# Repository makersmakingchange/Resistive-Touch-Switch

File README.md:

# Resistive Touch Switch

The Resistive Touch Switch is an open-source assistive switch that is activated through skin contact. The switch requires minimal force to activate.

## More info at

- [Makers Making Change Project Page](https://www.makersmakingchange.com/project/resistive-touch-switch/)

<!-- ABOUT MMC START -->
## About Makers Making Change

Makers Making Change is a program of [Neil Squire](https://www.neilsquire.ca/), a Canadian non-profit that uses technology, knowledge, and passion to empower people with disabilities.

Makers Making Change leverages the capacity of community based Makers, Disability Professionals and Volunteers to develop and deliver affordable Open Source Assistive Technologies.

 - Website: [www.MakersMakingChange.com](https://www.makersmakingchange.com/)
 - GitHub: [makersmakingchange](https://github.com/makersmakingchange)
 - Bluesky: [@makersmakingchange.bsky.social](https://bsky.app/profile/makersmakingchange.bsky.social)
 - Instagram: [@makersmakingchange](https://www.instagram.com/makersmakingchange)
 - Facebook: [makersmakechange](https://www.facebook.com/makersmakechange)
 - LinkedIn: [Neil Squire Society](https://www.linkedin.com/company/neil-squire-society/)
 - Thingiverse: [makersmakingchange](https://www.thingiverse.com/makersmakingchange/about)
 - Printables: [MakersMakingChange](https://www.printables.com/@MakersMakingChange)

### Contact Us
For technical questions, to get involved, or to share your experience we encourage you to [visit our website](https://www.makersmakingchange.com/) or [contact us](https://www.makersmakingchange.com/s/contact).
<!-- ABOUT MMC END -->

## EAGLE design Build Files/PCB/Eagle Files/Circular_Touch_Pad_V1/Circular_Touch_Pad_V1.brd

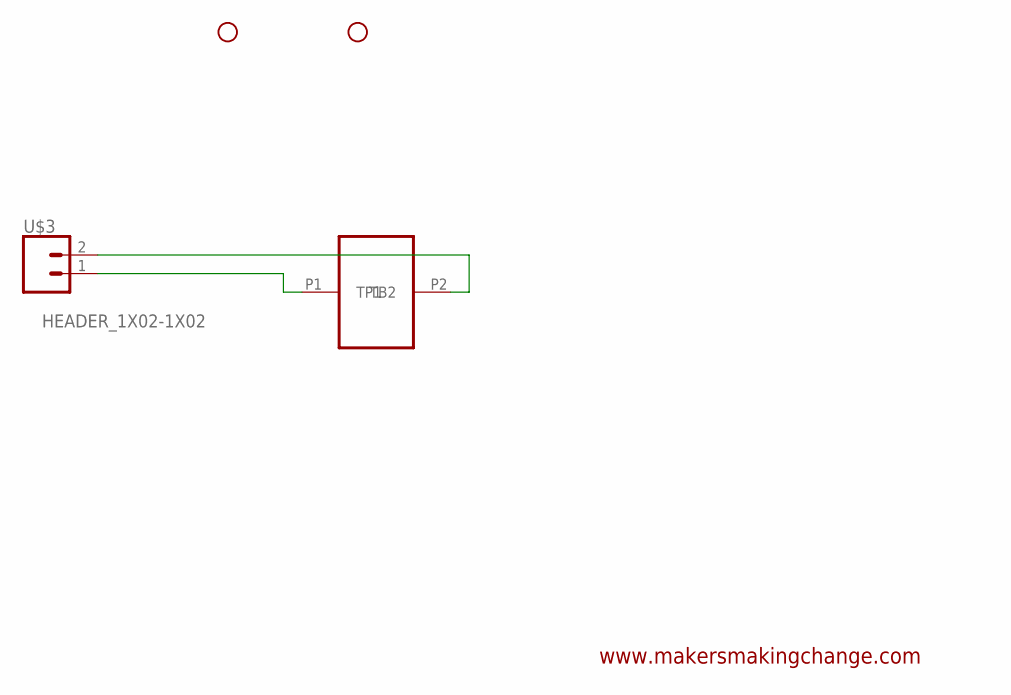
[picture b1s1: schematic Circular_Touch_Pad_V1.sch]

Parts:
H1, H2: STAND-OFF-; STAND-OFF
U$1: TOUCHPAD-CIRCLE; TOUCHPAD-CIRCLE-VER1
U$3: HEADER_1X02-1X02; 1X02

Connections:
unnamed: U$1.P1 (TP1), U$3.1
unnamed: U$1.P2 (TB2), U$3.2

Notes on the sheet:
www.makersmakingchange.com

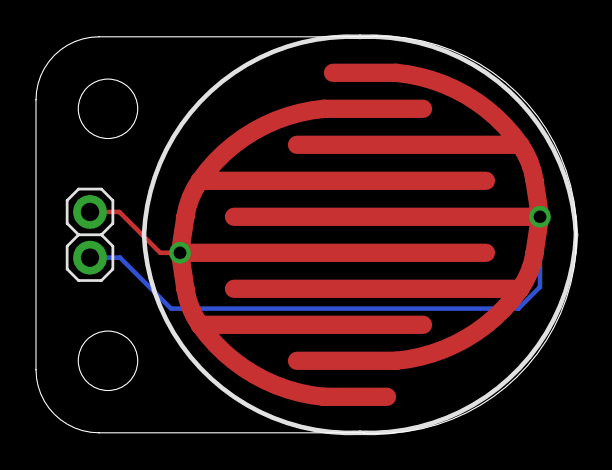
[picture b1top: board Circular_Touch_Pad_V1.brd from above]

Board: 2 copper layers, 30.0 x 22.1 mm, 4 parts (0 on the bottom side), 2 nets.

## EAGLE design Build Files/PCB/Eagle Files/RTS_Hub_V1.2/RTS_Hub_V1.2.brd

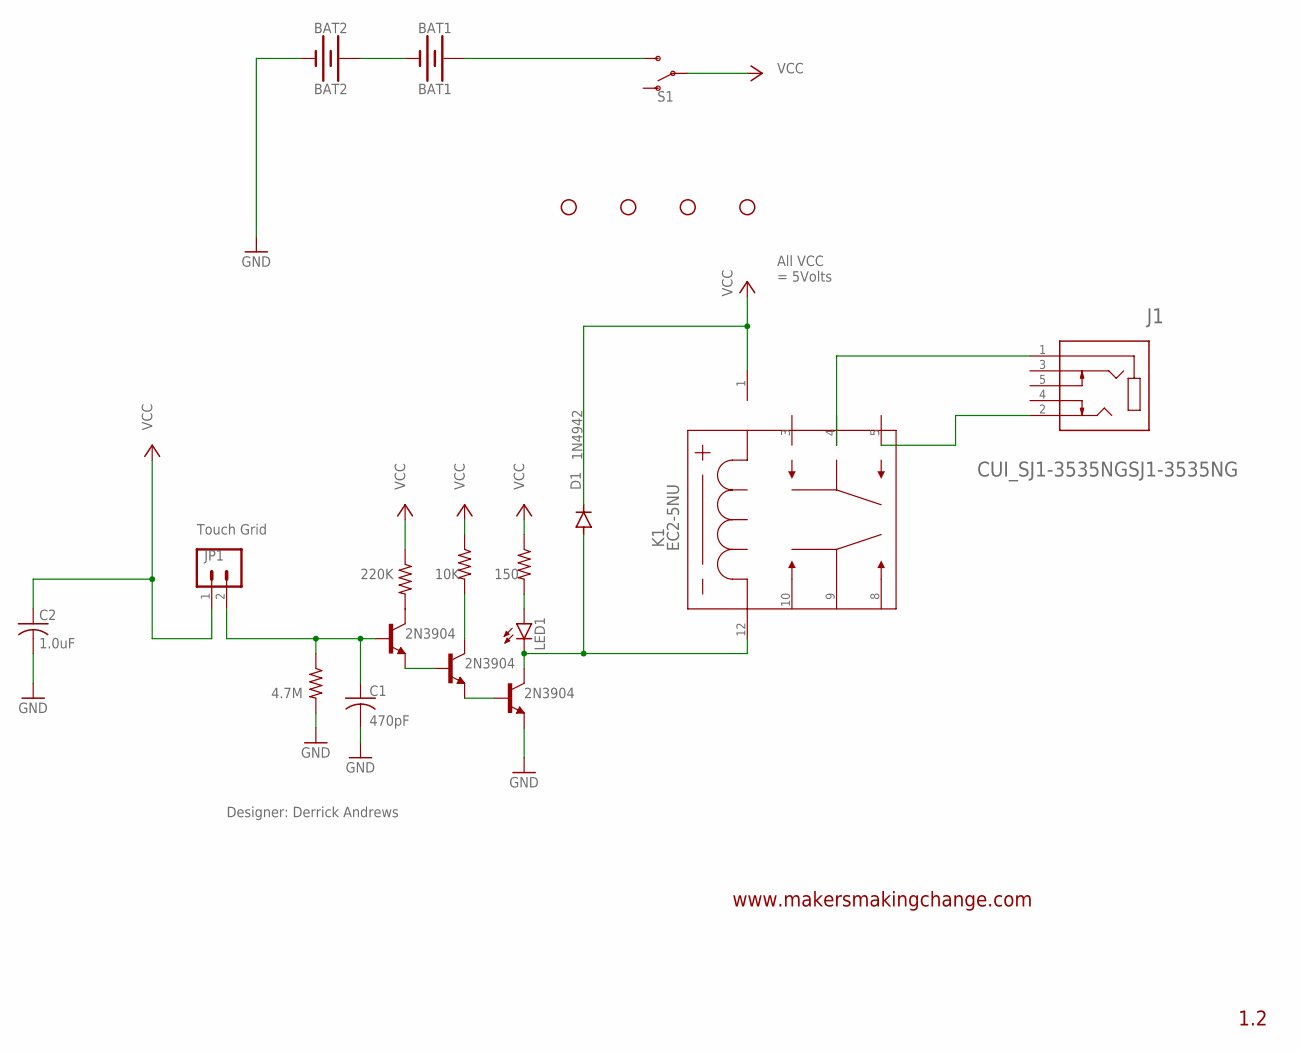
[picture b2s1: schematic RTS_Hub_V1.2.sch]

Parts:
BAT1: BAT1; BATTCOM_20MM_PTH
BAT2: BAT2; BATTCOM_20MM_PTH
C1: 470pF; C025-030X050
C2: 1.0uF; C050-030X075
D1: 1N4942; DO41-10
H1, H2, H3, H4: STAND-OFF-; STAND-OFF
J1: CUI_SJ1-3535NGSJ1-3535NG; CUI_SJ1-3535NG
JP1: HEADER_1X02-1X02; 1X02
K1: EC2-5NU; EC2NU
LED1: LED5MM; LED_5MM
R1: 10K; RESISTOR_0207/7
R2: 4.7M; RESISTOR_0207/7
R3: 220K; RESISTOR_0207/7
R4: 150; RESISTOR_0207/7
S1: SWITCH-SPDT-PTH_11.6X4.0MM; SWITCH_SPDT_PTH_11.6X4.0MM
T1, T2, T3: 2N3904; TO92-CBE

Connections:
GND: BAT2.-, C1.2, C2.2, R2.2, T1.E
unnamed: T2.B, T3.E
unnamed: T1.B, T2.E
unnamed: D1.A, K1.12 (8), LED1.K (C), T1.C
unnamed: R1.2, T2.C
unnamed: R3.2, T3.C
unnamed: LED1.A, R4.2
unnamed: C1.1, JP1.2, R2.1, T3.B
unnamed: BAT1.+, S1.3 (S)
unnamed: J1.1, K1.4 (3)
unnamed: J1.2, K1.5 (4)
unnamed: BAT1.-, BAT2.+
VCC: C2.1, D1.C, JP1.1, K1.1, R1.1, R3.1, R4.1, S1.2

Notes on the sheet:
150
220K
10K
Touch Grid
4.7M
All VCC = 5Volts
Designer: Derrick Andrews
www.makersmakingchange.com
1.2

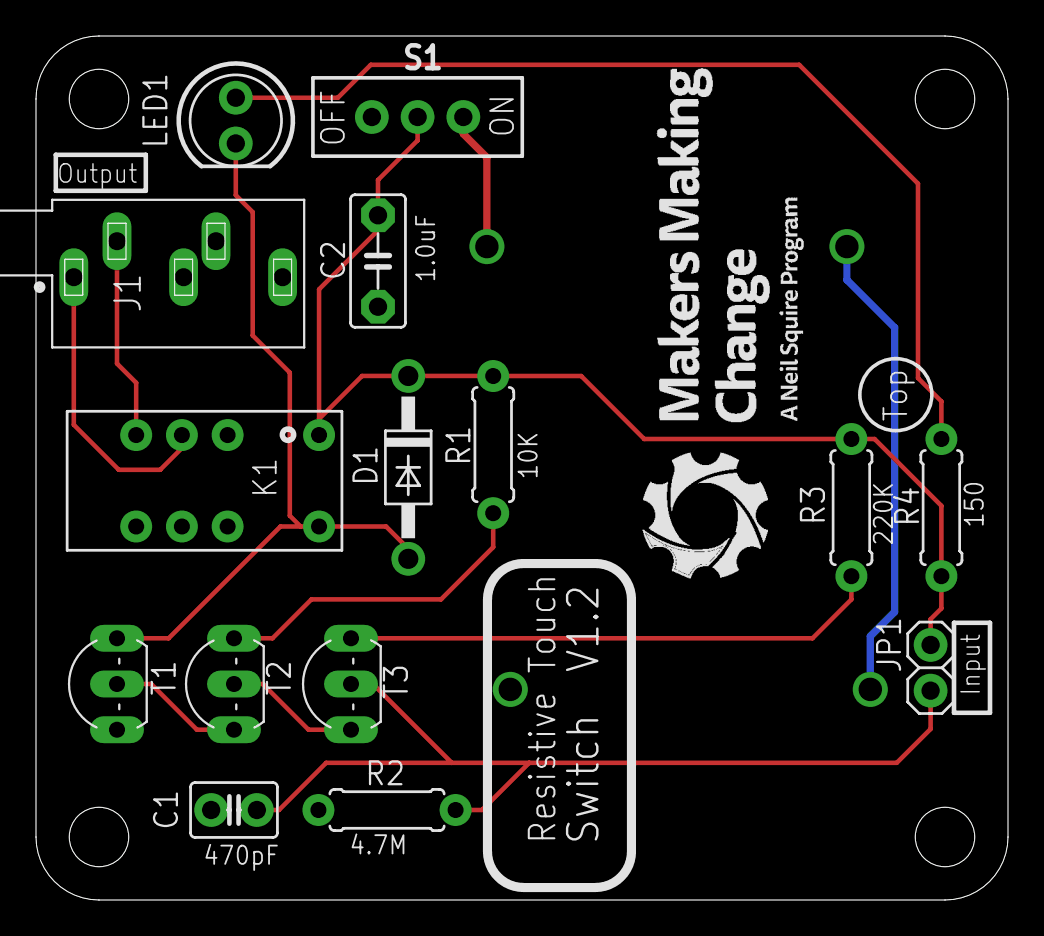
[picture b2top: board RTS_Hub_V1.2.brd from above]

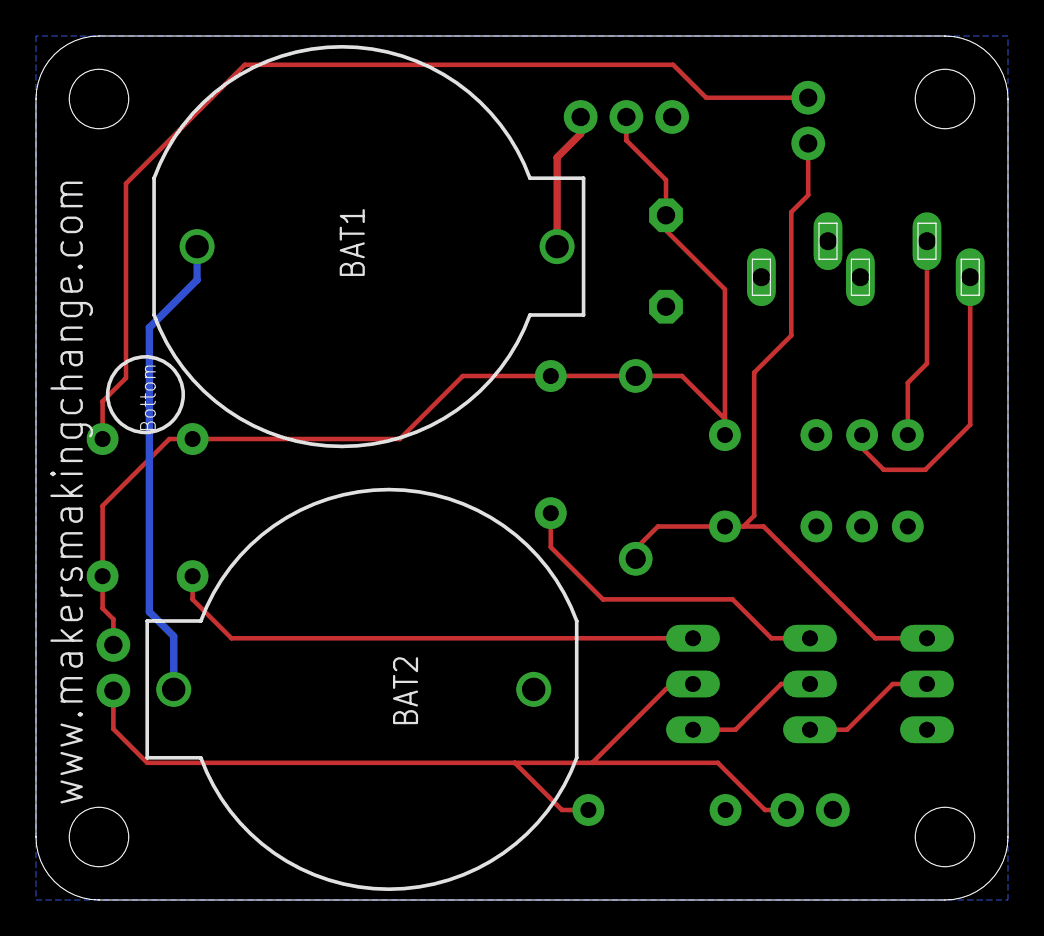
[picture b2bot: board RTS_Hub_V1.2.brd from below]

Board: 2 copper layers, 54.0 x 48.0 mm, 21 parts (2 on the bottom side), 13 nets.

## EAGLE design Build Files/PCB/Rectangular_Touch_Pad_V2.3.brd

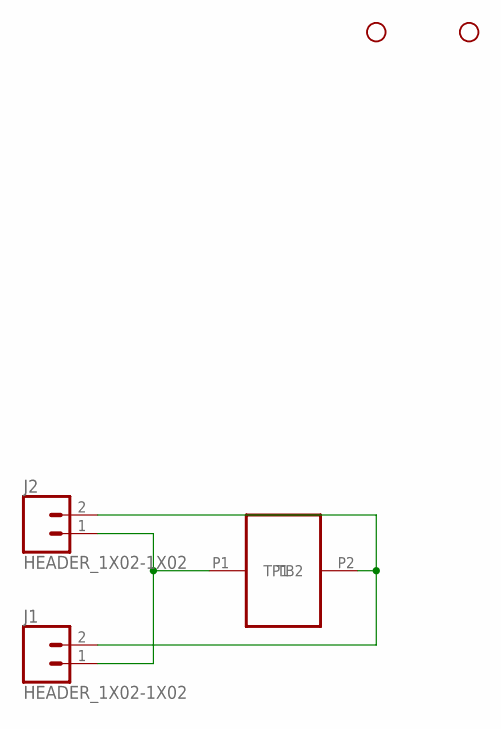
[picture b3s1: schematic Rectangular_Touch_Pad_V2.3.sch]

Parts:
H1, H2: STAND-OFF-; STAND-OFF
J1, J2: HEADER_1X02-1X02; 1X02
U$1: TOUCHPAD-VER2.3; TOUCHPAD-RECT-VER2.3

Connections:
unnamed: J1.1, J2.1, U$1.P1 (TP1)
unnamed: J1.2, J2.2, U$1.P2 (TB2)

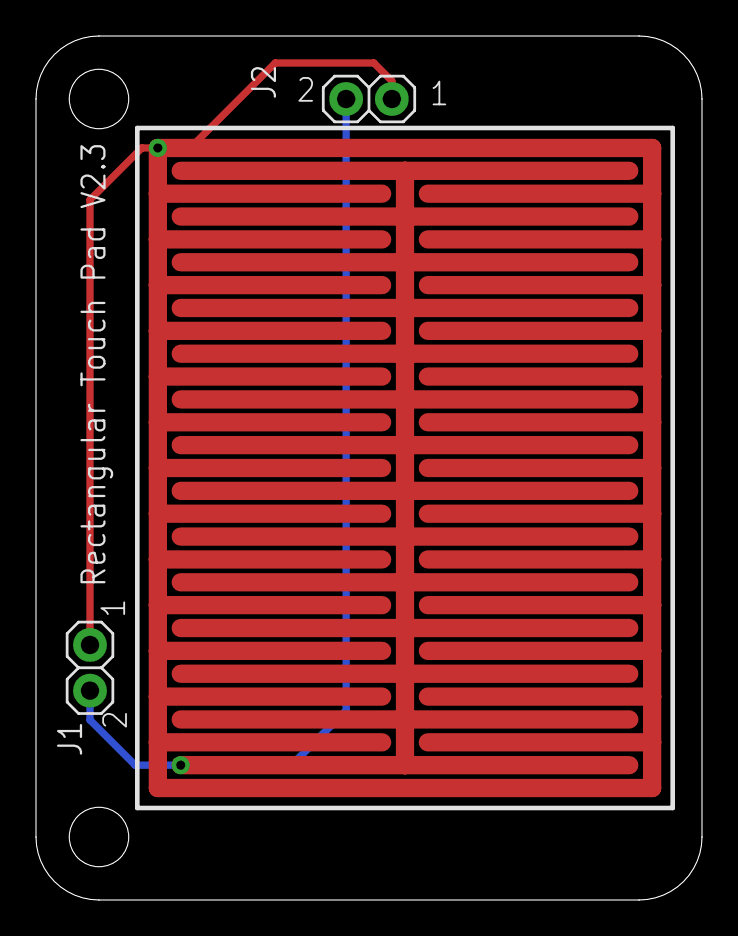
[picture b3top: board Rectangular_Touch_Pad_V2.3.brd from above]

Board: 2 copper layers, 37.0 x 48.0 mm, 5 parts (0 on the bottom side), 2 nets.

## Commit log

2020-04-01 :tada: Added .gitattributes & .gitignore files
2020-04-06 Update build files.
2020-04-21 Updated PCB files and added gerber files
2020-05-07 Correct folder names
2020-05-07 Cleanup
2020-05-07 Gerber files and PCB files
2020-05-08 Added the PCB Fabrication Manual
2020-05-08 Add missing stl files
2020-05-08 Create RTS_3DPrint_Orientation.jpg
    Add photo of intented print orientation.
2020-05-08 Create README.md
    Add 3D printing info readme
2020-05-13 Update pdf file names.
2025-04-10 Add Update About MMC GitHub Action
2025-04-12 Update About MMC Section
